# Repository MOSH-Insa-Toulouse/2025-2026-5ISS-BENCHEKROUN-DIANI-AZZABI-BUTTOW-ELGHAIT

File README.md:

# Gas Sensor - IoT Project

This project presents the complete development of an IoT gas sensor system, encompassing the entire pipeline from chemical synthesis to cloud integration. The work includes:

- **Chemical production** of WO₃ (tungsten trioxide) nanoparticle-based gas sensors in the laboratory
- **Electrical characterization** and datasheet development
- **LoRaWAN communication** testing with Arduino microcontroller
- **Node-RED integration** for real-time data visualization and monitoring
- **PCB system design** for the complete electronic circuit
- **Mobile application** development for user interaction

This multidisciplinary approach demonstrates a complete IoT solution from sensor fabrication to end-user interface.

## MOx Sensor Manufacturing

During a week at the AIME laboratory of INSA Toulouse, we fabricated our own MOx (Metal Oxide) gas sensor. This chapter describes how the MOx gas sensor was fabricated, from the micro-structure on the chip to the final packaged component ready for tests. The main goal is to build a sensor with interdigitated electrodes and a metal-oxide active layer (WO₃), and to make sure it can be electrically connected and handled safely during measurements.

### 1.1 MOx Sensor Architecture

The sensor is based on a small chip that includes a heating element (to control the operating temperature) and metal electrodes where the metal-oxide material will be deposited. The device is designed so that the gas-sensitive layer can change its resistance depending on the surrounding atmosphere.

### 1.2 Photolithography

First, the polysilicon heating element (used to heat the MOx resistor, lower its resistance, and remove water residues) was already manufactured in the AIME clean room by professionals. It was obtained by depositing a polysilicon layer and then patterning it using a photoresist mask activated by UV light.

Then, metallization was performed by depositing a thin aluminum layer (about 500 nm) to create electrodes and electrical contacts. After that, metal etching defined the final electrode patterns by removing unwanted aluminum. This step used a resist coating, UV exposure with a mask, development, annealing cycles, and a chemical etching bath, with microscope inspections to verify quality after each stage.

### 1.3 Metal Oxide (MOx) Synthesis

The active sensing material is tungsten trioxide (WO₃). The synthesis process consists of two steps: first, seed preparation (chemical mixing and centrifugation to collect the precipitate), and second, nanowire growth using a hydrothermal process at high temperature, followed by rinsing and storage. This method aims to produce homogeneous nanostructures suitable for gas sensing.

To place the WO₃ nanoparticles onto the interdigitated electrodes, dielectrophoresis is used: a small drop of nanoparticle solution is deposited on the chip, and an AC voltage is applied to align the particles between the electrodes. After rinsing and drying, the chip is checked under an optical microscope to confirm a uniform and well-aligned active layer.

### 1.4 Packaging

Finally, the sensor is packaged using a JEDEC TO-5 metal can package with 10 pins. The chip is placed on a glass support to provide electrical isolation, and wire bonding is used to connect the chip pads to the package pins. This creates a robust component that can be connected to external electronics for characterization and integration.

## Sensor Characterization

After fabricating the sensor, we characterized two key parts of the device: the integrated thermistor (used to estimate temperature) and the MOx gas-sensing resistance (WO₃). The goal is to obtain practical electrical values that can later be used for conditioning, calibration, and integration into electronics.

### 2.1 Thermistor

The thermistor (called R_alu) is treated as a PTC component, meaning its resistance increases with temperature. Since it was not fully characterized, we assumed an approximate coefficient of 1 Ω per °C, based on a similarity with a Pt100-like behavior. A proper method would be to heat it while comparing with a reference thermometer, but this was not done, and the approximation was considered "good enough" for operating the MOx sensor.

To find the room-temperature reference resistance, we measured an I-V curve using a waveform generator and an instrumentation setup, then applied Ohm's law. The nominal resistance obtained was about 86 Ω at ambient temperature (around 21°C). We also observed non-linearity at higher voltage, likely caused by self-heating of the thermistor.

### 2.2 MOx Resistance

**Nominal resistance:** The WO₃ sensing layer has a very high resistance in its reduced form, in the GΩ range, which makes measurement difficult due to the need for a precise current source and because thermal noise becomes significant. As a result, the reported value is a rough estimate, but we obtained a typical resistance around 16 GΩ.

**Sensitivity to ethanol:** We performed an experiment to evaluate the sensor response to ethanol vapor. First, the sensor temperature is increased (around 550 K) to evaporate moisture and reduce resistance. Then the test is performed in two phases: a regeneration phase under dry air (to "regenerate" the sensor surface), followed by a detection phase under an ethanol/air mixture (about 1000 ppm). During exposure, the resistance drops with an exponential-like behavior.

From this test, we extracted several performance indicators, including:
- **Relative resistance change:** approximately 64% for our test conditions
- **Sensitivity coefficient:** based on (R_air - R_eth)/R_air
- **Response time:** about 88 seconds to reach 10% of the final value
- **Sensitivity:** 85,000 Ω/ppm
- **Detection limit:** approximately 38.3 ppm, based on the Arduino ADC resolution (10-bit), amplifier gain, and the measured sensitivity

## Integration into a Smart Device

This chapter focuses on how we integrated the MOx gas sensor into a smart embedded device using an Arduino as the main controller. The objective was to build a system able to read the sensor through an adapted analog front-end, and to prepare the hardware for a future connected version.

### 3.1 Arduino-based Prototype (Hardware Concept)

Because the final PCB/shield could not be manufactured in time, we used a prototype setup where an Arduino would interface with the gas sensor through signal conditioning. We temporarily relied on a commercial Grove gas sensor to keep the integration moving while the custom MOx board was still under development.

The system was implemented using Arduino Uno with the following sensors:
- **Temperature and humidity sensor** - for environmental monitoring
- **Grove gas sensor** - commercial reference sensor
- **Our MOx gas sensor** - sensor fabricated with WO₃ nanoparticles

### 3.2 Signal Conditioning for the MOx Sensor

Since the WO₃ sensing element can reach very high resistance (GΩ range), the sensor cannot be connected directly to the Arduino ADC. For this reason, we designed a dedicated conditioning stage (based on a transimpedance/very high gain approach) that converts the sensor behavior into a measurable voltage range for the Arduino. We validated this front-end using LTSpice simulations, and we highlight the main challenge: at such high impedance, noise becomes significant, which can limit measurement quality.

### 3.3 Filters and Noise Considerations

To improve stability, we included RC filtering at different points (input/output/feedback and power supply). The theoretical and simulated cut-off frequencies were designed to reduce low-frequency drift and attenuate noise sources such as mains-related interference (50 Hz) and EMC disturbances.

### 3.4 Arduino Code Implementation

The Arduino code (`OpenSource_V2.4.ino`) performs:
- Gas sensor reading on pin A0
- LoRaWAN communication through The Things Network (TTN)
- OLED display for local data visualization
- LED alert system when gas values exceed the threshold

**Main code features:**
- Analog reading of the gas sensor (A0)
- Alert threshold: GAZ_VALUE > 100
- Data transmission via LoRaWAN every 10 seconds
- OLED display for visual feedback
- LED alert for gas detection

## Node-RED

The Node-RED system was implemented to receive and process sensor data through the MQTT protocol, connecting to ChirpStack/The Things Network. This provides a visual programming interface for data flow management and real-time monitoring of the gas sensor system.

### 4.1 System Architecture

The Node-RED implementation creates a complete IoT data pipeline that:
- Subscribes to MQTT topics from the LoRaWAN network server (ChirpStack/TTN)
- Processes incoming sensor data in real-time
- Provides visual dashboards for monitoring
- Implements alert logic based on sensor thresholds
- Stores historical data for analysis

### 4.2 MQTT Integration

The system uses an MQTT input node configured to subscribe to the application-specific topic:
- **Topic pattern**: `application/[app-id]/device/+/event/up`
- **QoS Level**: 2 (exactly once delivery)
- **Protocol**: MQTT over ChirpStack/The Things Network

This ensures reliable reception of all uplink messages from the deployed gas sensors in the field.

### 4.3 Data Processing Flow

The implemented flow performs several processing stages:

1. **Message Filtering**: Filters only uplink events (`/event/up`) to ignore other event types
2. **Base64 Decoding**: Extracts and decodes the base64-encoded payload from the LoRaWAN message
3. **Payload Parsing**: Interprets the binary data structure:
   - Byte 0: Sensor ID (identifies which sensor sent the data)
   - Bytes 1-2: 16-bit big-endian integer containing the raw sensor value
   - Conversion: Divides raw value by 100 to obtain the actual measurement
4. **Alert Logic**: Implements threshold-based alerting:
   - Normal operation: value ≤ 80
   - Alert state: value > 80 (triggers "Help" notification)
5. **Data Distribution**: Routes processed data to multiple outputs (debug console, dashboard widgets, data storage)

### 4.4 Node-RED Flow

The visual flow includes:
- MQTT subscriber node for data ingestion
- Function nodes for data transformation and business logic
- Debug nodes for development and troubleshooting
- Dashboard UI nodes for real-time visualization
- Chart nodes for historical trend display

### 4.5 Dashboard

The Node-RED dashboard provides a web-based interface for real-time monitoring with:

**Display Elements:**
- **Current sensor value**: Real-time display of gas concentration readings
- **Alert status**: Visual indicator showing "Normal" or "Help" states
- **Historical chart**: Time-series graph showing sensor readings over time
- **Sensor identification**: Displays which sensor (by ID) is reporting

**Features:**
- Responsive web interface accessible from any device
- Automatic updates as new data arrives
- Color-coded alerts for quick status assessment
- Historical data visualization for trend analysis

### 4.6 Implementation Details

The complete flow configuration is available in the `flows.json` file, which can be imported directly into Node-RED for deployment. The implementation uses standard Node-RED nodes along with the dashboard palette for UI components, making it easy to customize and extend for additional features or sensors.

## The electrical circuit
Here is the complete electrical diagram of our system. It consists of a gas-type switch, a variable resistor using an MCP41100 digital potentiometer, another variable resistor using an MCP41100 digital potentiometer, an Arduino Uno, a gas sensor, and a LoRa module.

The fabricated gas sensor exhibits a very high resistance that varies depending on the type and presence of gas. Its resistance is on the order of gigohms, resulting in an extremely low current of the order of nanoamperes flowing into the ADC. Since an Arduino uses a 10-bit ADC, the sensor output signal must be amplified. To address this, we designed an amplification circuit based on an operational amplifier and validated it through LTSpice simulations.
Below is the LTSpice circuit:

The circuit includes three filters with different cutoff frequencies to reduce noise and shape the signal:
- A low-frequency filter to suppress sensor noise,
- A notch filter to attenuate 50 Hz power-line interference,
- An anti-aliasing filter to prevent distortion during ADC sampling.

Transient simulations confirmed correct amplifier operation, with a gain of 101, matching theoretical calculations. Frequency analysis using Bode diagrams showed an overall gain of 140 dB, consistent with the expected transfer function. FFT analysis further demonstrated effective noise reduction, particularly at 50 Hz, while highlighting the trade-off between noise suppression and signal distortion when filter capacitance is increased excessively.
Overall, the simulations validate the amplifier design and confirm its suitability for accurately measuring low-current gas sensor signals using low-cost data acquisition systems.

## PCB Design
To bring all the components of our sensor system together, we designed a dedicated Printed Circuit Board (PCB). This board combines all stages of the system into a unified and compact design, providing an optimized layout, enhanced reliability, and efficient operation. The detailed PCB design is shown in the figure below.

Below, there is a 3D view of the PCB after conception.

- Front view:

- Back view:

## MIT App Inventor

The MIT App Inventor application is designed to interface with the Arduino, allowing users to control the system and monitor sensor data in real time.

This MIT App Inventor application functions as a Bluetooth remote control for an Arduino system. It allows the user to first connect to a Bluetooth module (such as HC-05) through a list of available devices, and then send commands either by pressing buttons or using voice commands. The "LED ON" button sends the number 1 to turn on the LED, the "LED OFF" button sends 2 to turn it off, and if the voice recognition detects the word "blink," the app sends 3 to make the LED blink. At the same time, the application can receive and display messages sent by the Arduino via Bluetooth.

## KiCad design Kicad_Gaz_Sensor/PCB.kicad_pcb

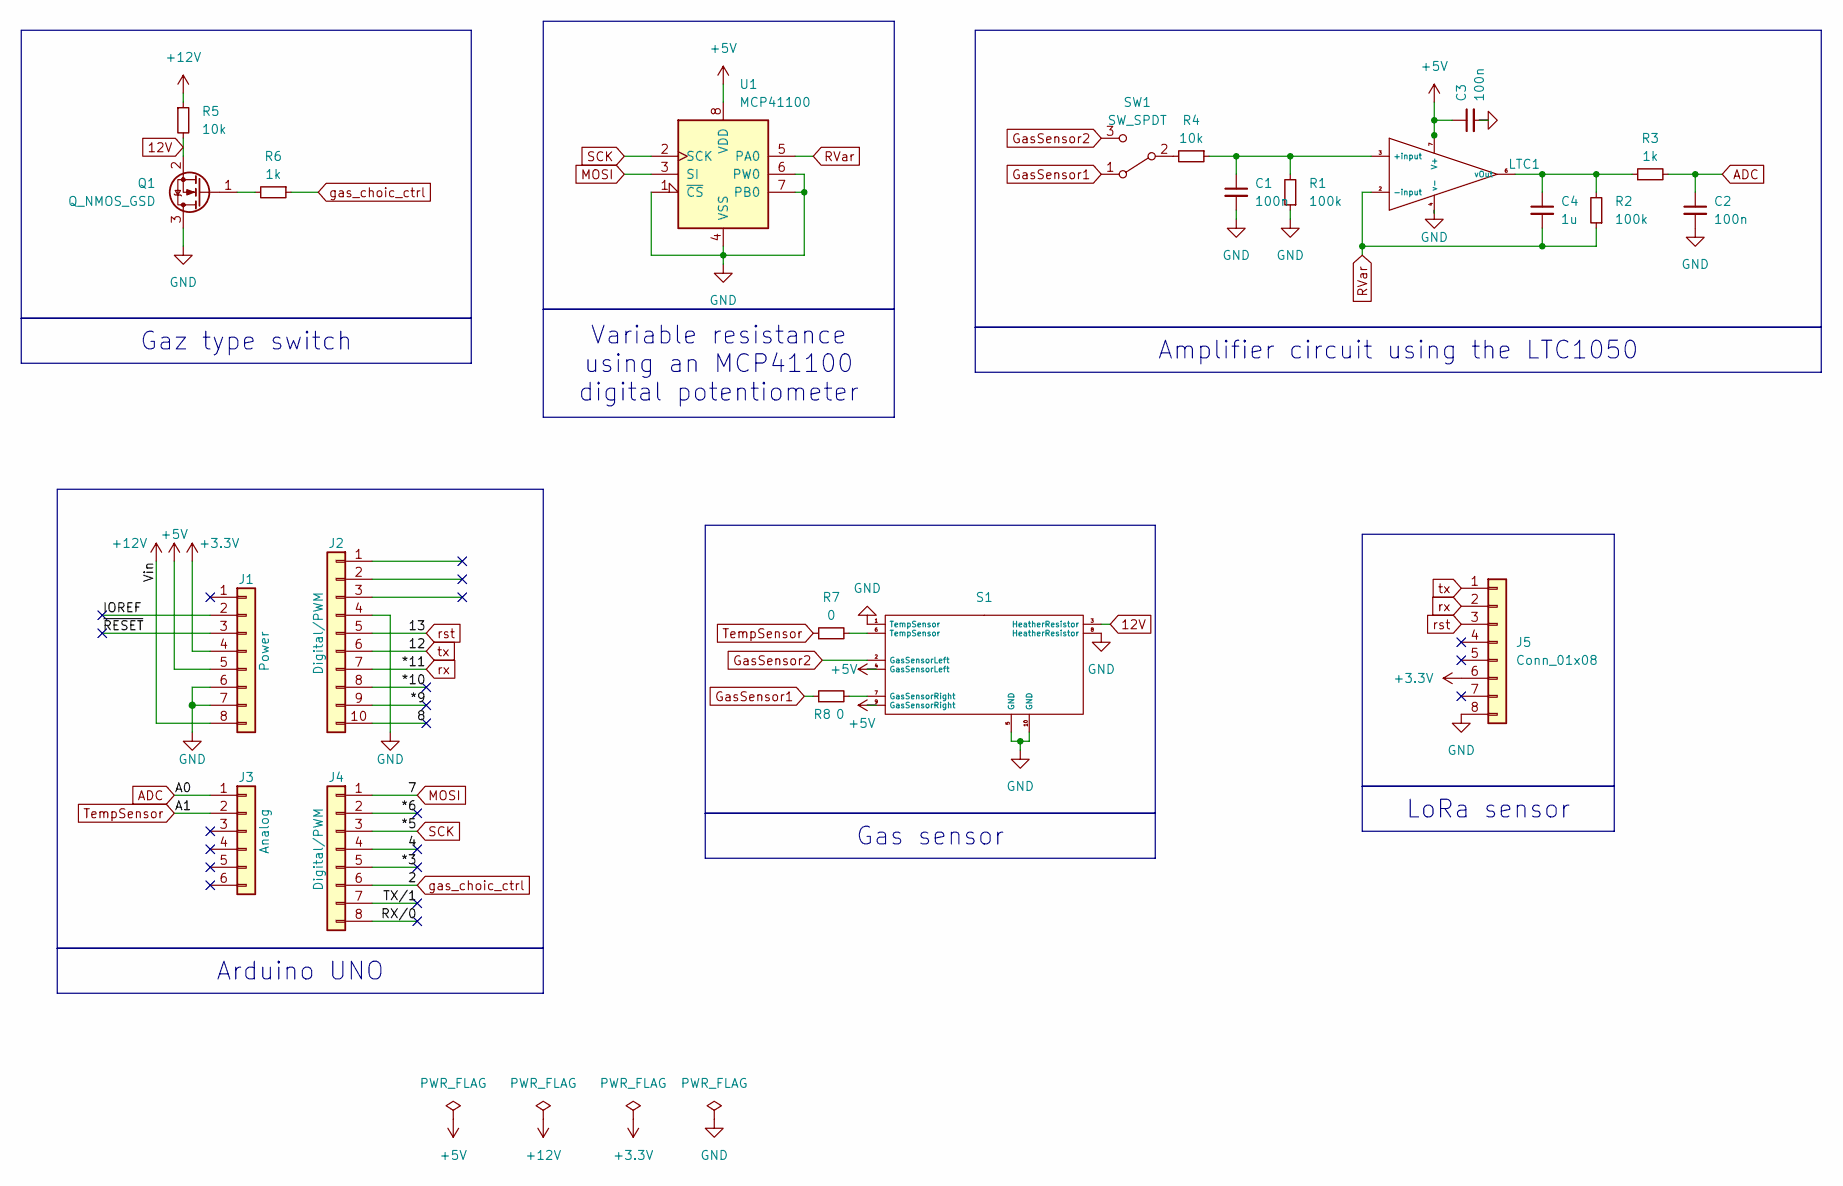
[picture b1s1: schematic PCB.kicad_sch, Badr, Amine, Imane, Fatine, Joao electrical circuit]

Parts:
C1, C2, C3: 100n; C_Disc_D3.0mm_W1.6mm_P2.50mm
C4: 1u; C_Disc_D3.0mm_W1.6mm_P2.50mm
J1: Power; PinSocket_1x08_P2.54mm_Vertical
J2: Digital/PWM; PinSocket_1x10_P2.54mm_Vertical
J3: Analog; PinSocket_1x06_P2.54mm_Vertical
J4: Digital/PWM; PinSocket_1x08_P2.54mm_Vertical
J5: Conn_01x08; PinSocket_1x08_P2.54mm_Vertical
LTC1: DIP-8_W7.62mm_LongPads
Q1: Q_NMOS_GSD; TO-220-3_Vertical
R1, R2: 100k; R_Axial_DIN0204_L3.6mm_D1.6mm_P5.08mm_Horizontal
R3, R6: 1k; R_Axial_DIN0204_L3.6mm_D1.6mm_P5.08mm_Horizontal
R4, R5: 10k; R_Axial_DIN0204_L3.6mm_D1.6mm_P5.08mm_Horizontal
R7, R8: 0; R_Axial_DIN0204_L3.6mm_D1.6mm_P5.08mm_Horizontal
S1: TO-5-10_Window
SW1: SW_SPDT; SW_Push_2P2T_Toggle_CK_PVA2xxH2xxxxxxV2
U1: MCP41100; DIP-8_W7.62mm

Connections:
12V: Q1.2 (S), R5.2, S1.3 (HeatherResistor)
+3.3V: J1.4, J5.6
+5V: C3.1, J1.5, LTC1.7 (V+), S1.4 (GasSensorLeft), S1.9 (GasSensorRight), U1.8 (VDD)
+12V: J1.8, R5.1
/4: J4.4
/8: J2.10
/*3: J4.5
/*6: J4.2
/*9: J2.9
/*10: J2.8
/IOREF: J1.2
/RX/0: J4.8
/TX/1: J4.7
/~RESET: J1.3
ADC: C2.1, J3.1, R3.2
GND: C1.2, C2.2, C3.2, J1.6, J1.7, J2.4, J5.8, LTC1.4 (v-), Q1.3 (D), R1.1, S1.1 (TempSensor), S1.5 (GND), S1.8 (HeatherResistor), S1.10 (GND), U1.1 (~CS), U1.4 (VSS), U1.6 (PW0), U1.7 (PB0)
GasSensor1: R8.1, SW1.1 (A)
GasSensor2: S1.2 (GasSensorLeft), SW1.3 (C)
MOSI: J4.1, U1.3 (SI)
unnamed: C1.1, LTC1.3 (+input), R1.2, R4.1
unnamed: C4.1, LTC1.6 (vOut), R2.2, R3.1
unnamed: Q1.1 (G), R6.2
unnamed: R7.2, S1.6 (TempSensor)
unnamed: R8.2, S1.7 (GasSensorRight)
unnamed: R4.2, SW1.2 (B)
RVar: C4.2, LTC1.2 (-input), R2.1, U1.5 (PA0)
SCK: J4.3, U1.2 (SCK)
TempSensor: J3.2, R7.1
gas_choic_ctrl: J4.6, R6.1
rst: J2.5, J5.3
rx: J2.7, J5.2
tx: J2.6, J5.1

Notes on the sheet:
Gas sensor
Amplifier circuit using the LTC1050
LoRa sensor
Variable resistance using an MCP41100 digital potentiometer
Arduino UNO
Gaz type switch

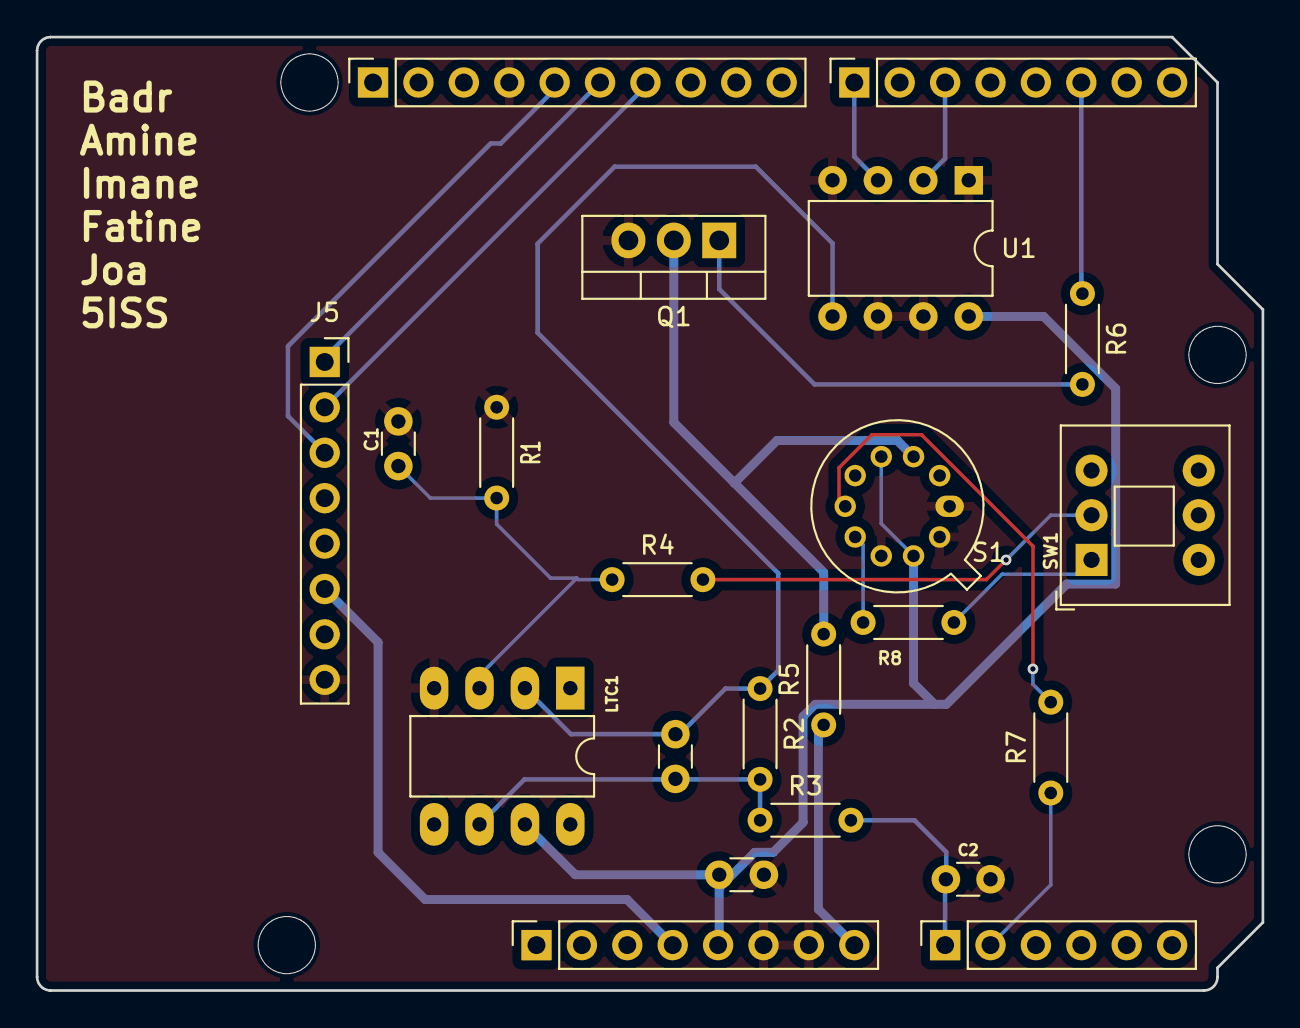
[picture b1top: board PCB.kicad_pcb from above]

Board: 2 copper layers, 68.6 x 53.3 mm, 26 parts (0 on the bottom side), 22 nets.

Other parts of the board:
MH1, MH2, MH3, MH4: MountingHole_3.2mm

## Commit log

2026-01-12 Create Arduino_code
2026-01-12 Create README with system overview and details
    Added detailed documentation on the electrical circuit, PCB design, and MIT App Inventor application for the sensor system.
2026-01-12 Update front view image dimensions in README
2026-01-21 Update README with new images and app details
    Updated images in the README to reflect recent changes and improvements in the electrical circuit and PCB design sections. Added details about the MIT App Inventor application functionalities.
2026-01-21 Add Arduino code, Node-RED flows, and assets
    Initial commit with Arduino sensor code, Node-RED flow configuration, dashboard images, and gas sensor datasheet. Enables LoRaWAN sensor data transmission and visualization via Node-RED dashboard.
2026-01-21 Initial plan
2026-01-21 Complete README with nanoparticle manufacturing, Arduino, and Node-RED sections
2026-01-21 Fix code block formatting and improve image placeholder comments
2026-01-21 Translate README content from Portuguese to English
2026-01-21 Update MOx sensor manufacturing section with detailed fabrication process
2026-01-21 Add sensor characterization section with thermistor and MOx resistance analysis
2026-01-21 Add image assets for Arduino and datasheets
    Added open_source.jpg to the Arduino directory and gas_sensor.jpeg and nanoscope.bmp to the Datasheet directory. These images may be used for documentation or reference purposes.
2026-01-21 Add Arduino integration chapter with signal conditioning and noise filtering details
2026-01-21 Expand Node-RED section with detailed architecture, MQTT integration, and data processing flow
2026-01-21 Rewrite introduction paragraph to comprehensively present the complete IoT system
2026-01-21 Improve introduction paragraph formatting with bullet points for better readability
2026-01-21 Fix image references to point to Datasheet folder for nanoscope and gas_sensor images
2026-01-25 Replace PCB images with updated versions
    Updated images in the PCB Design section with new captures.
2026-01-25 Modify PCB image size in README.md
    Updated PCB design image dimensions in README.
2026-01-25 Replace PCB images with updated versions
    Updated PCB design images with higher resolution and dimensions.
